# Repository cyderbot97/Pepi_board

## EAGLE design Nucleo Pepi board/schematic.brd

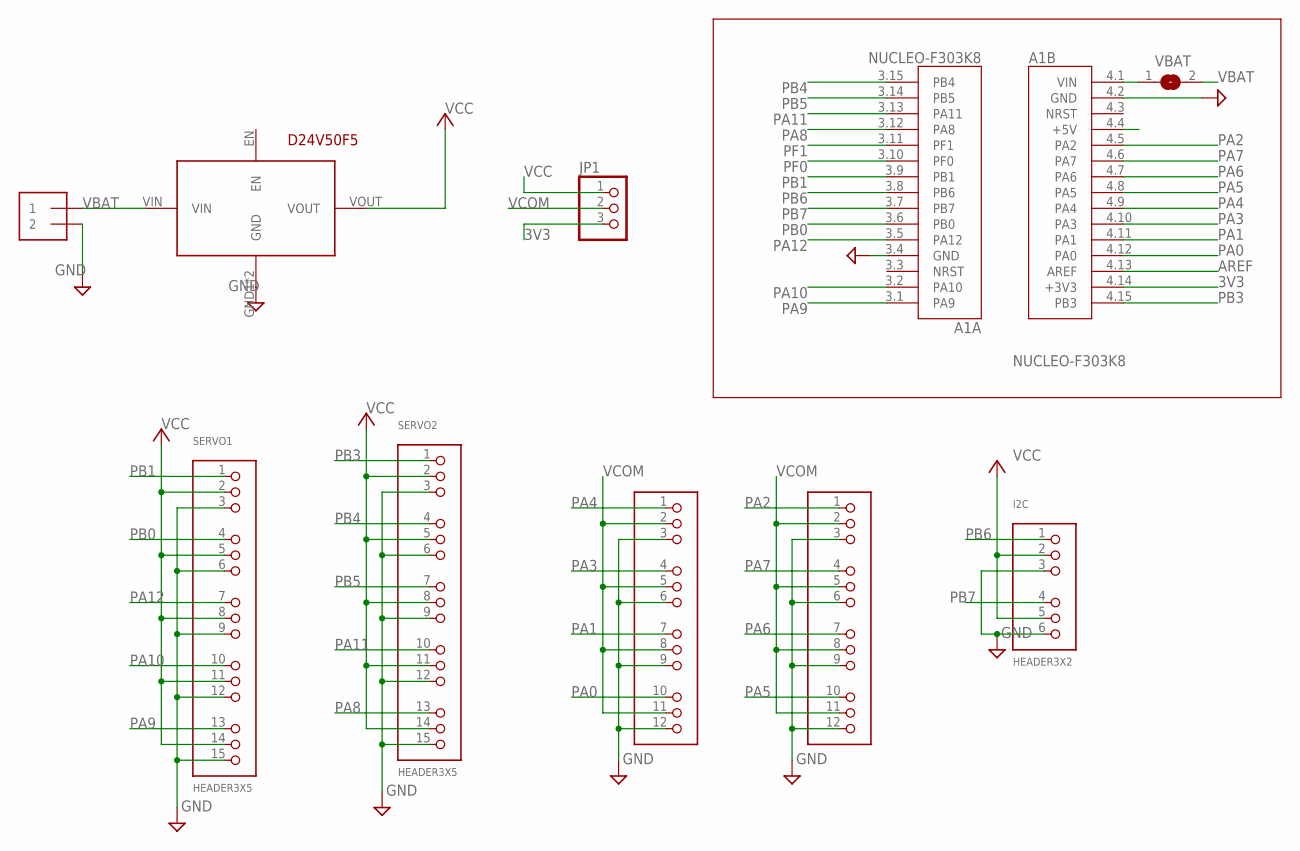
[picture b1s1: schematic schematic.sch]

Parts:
A1: NUCLEO-F303K8; MODULE_NUCLEO-F303K8
ADC: HEADER-3X04; 3X04
ADC_DAC: HEADER-3X04; 3X04
I2C: HEADER3X2
J1: 1X2-3.5MM
JP1: PINHD-1X3; 1X03
SERVO1, SERVO2: HEADER3X5
U$1: D24V50F5
VBAT: SJW

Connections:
3V3: A1.4.14 (+3V3), JP1.3
AREF: A1.4.13 (AREF)
GND: A1.3.4 (GND), A1.4.2 (GND), ADC.3, ADC.6, ADC.9, ADC.12, ADC_DAC.3, ADC_DAC.6, ADC_DAC.9, ADC_DAC.12, I2C.3, I2C.6, J1.2, SERVO1.3, SERVO1.6, SERVO1.9, SERVO1.12, SERVO1.15, SERVO2.3, SERVO2.6, SERVO2.9, SERVO2.12, SERVO2.15, U$1.GND1 (GND), U$1.GND2 (GND)
unnamed: A1.4.1 (VIN), VBAT.1
PA0: A1.4.12 (PA0), ADC.10
PA1: A1.4.11 (PA1), ADC.7
PA2: A1.4.5 (PA2), ADC_DAC.1
PA3: A1.4.10 (PA3), ADC.4
PA4: A1.4.9 (PA4), ADC.1
PA5: A1.4.8 (PA5), ADC_DAC.10
PA6: A1.4.7 (PA6), ADC_DAC.7
PA7: A1.4.6 (PA7), ADC_DAC.4
PA8: A1.3.12 (PA8), SERVO2.13
PA9: A1.3.1 (PA9), SERVO1.13
PA10: A1.3.2 (PA10), SERVO1.10
PA11: A1.3.13 (PA11), SERVO2.10
PA12: A1.3.5 (PA12), SERVO1.7
PB0: A1.3.6 (PB0), SERVO1.4
PB1: A1.3.9 (PB1), SERVO1.1
PB3: A1.4.15 (PB3), SERVO2.1
PB4: A1.3.15 (PB4), SERVO2.4
PB5: A1.3.14 (PB5), SERVO2.7
PB6: A1.3.8 (PB6), I2C.1
PB7: A1.3.7 (PB7), I2C.4
PF0: A1.3.10 (PF0)
PF1: A1.3.11 (PF1)
VBAT: J1.1, U$1.VIN, VBAT.2
VCC: I2C.2, I2C.5, JP1.1, SERVO1.2, SERVO1.5, SERVO1.8, SERVO1.11, SERVO1.14, SERVO2.2, SERVO2.5, SERVO2.8, SERVO2.11, SERVO2.14, U$1.VOUT
VCOM: ADC.2, ADC.5, ADC.8, ADC.11, ADC_DAC.2, ADC_DAC.5, ADC_DAC.8, ADC_DAC.11, JP1.2

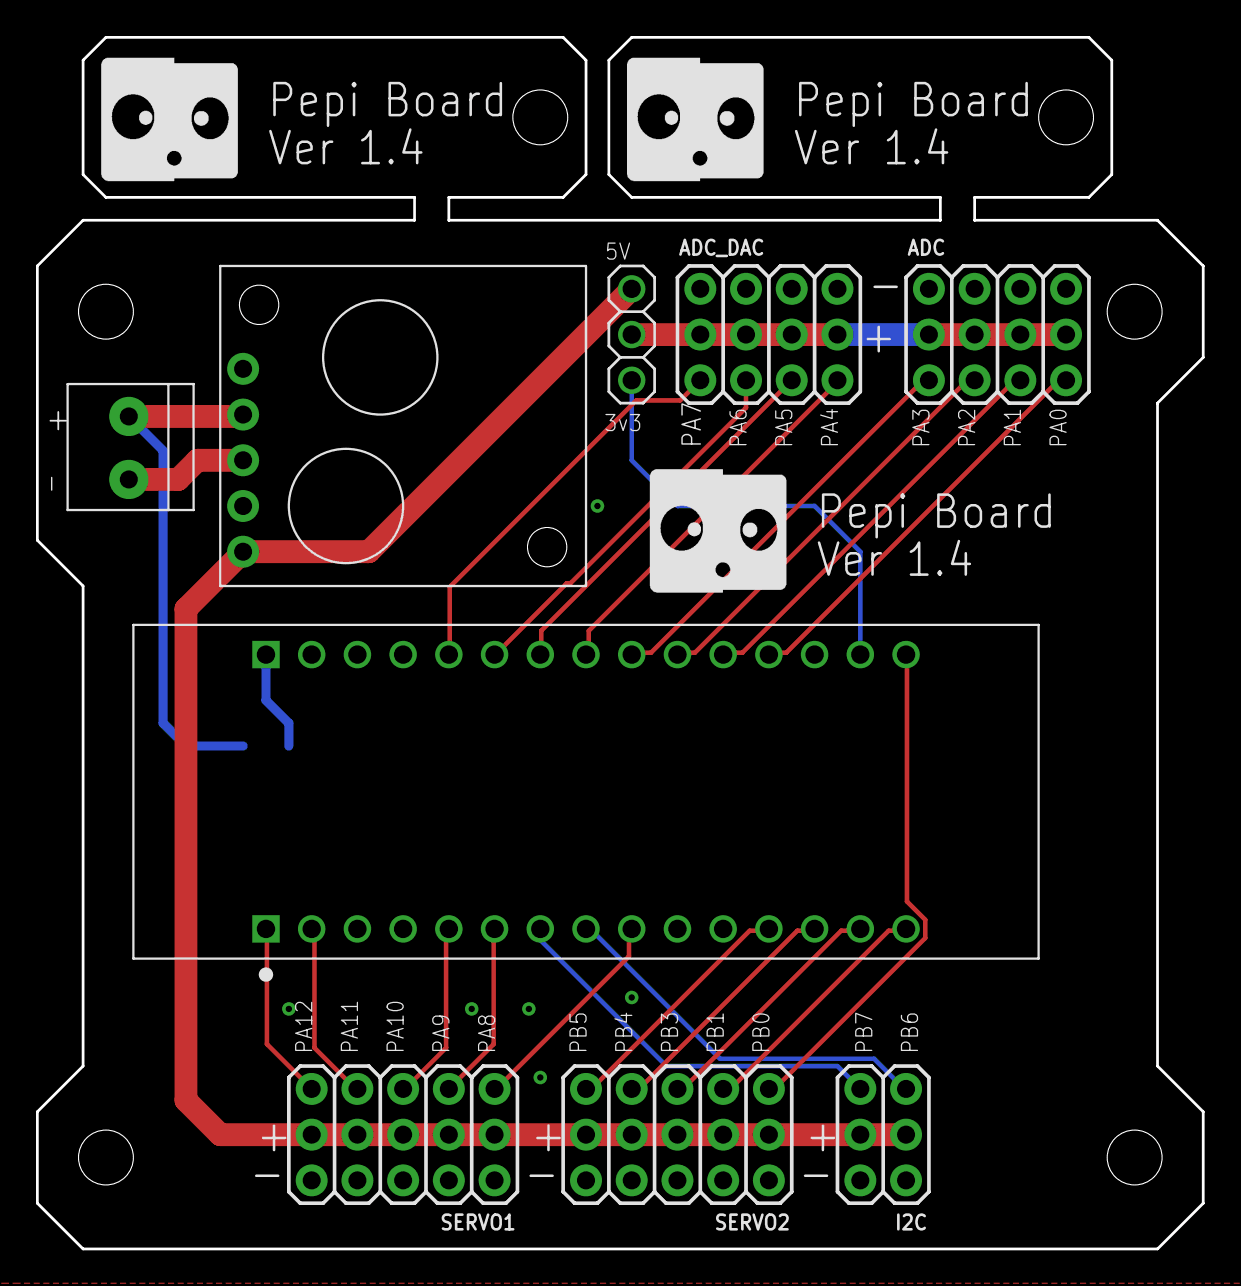
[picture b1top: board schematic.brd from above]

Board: 2 copper layers, 64.8 x 67.3 mm, 10 parts (1 on the bottom side), 26 nets.

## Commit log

2019-10-24 ver1.3
2019-11-22 update pc
2019-12-19 v1.4
